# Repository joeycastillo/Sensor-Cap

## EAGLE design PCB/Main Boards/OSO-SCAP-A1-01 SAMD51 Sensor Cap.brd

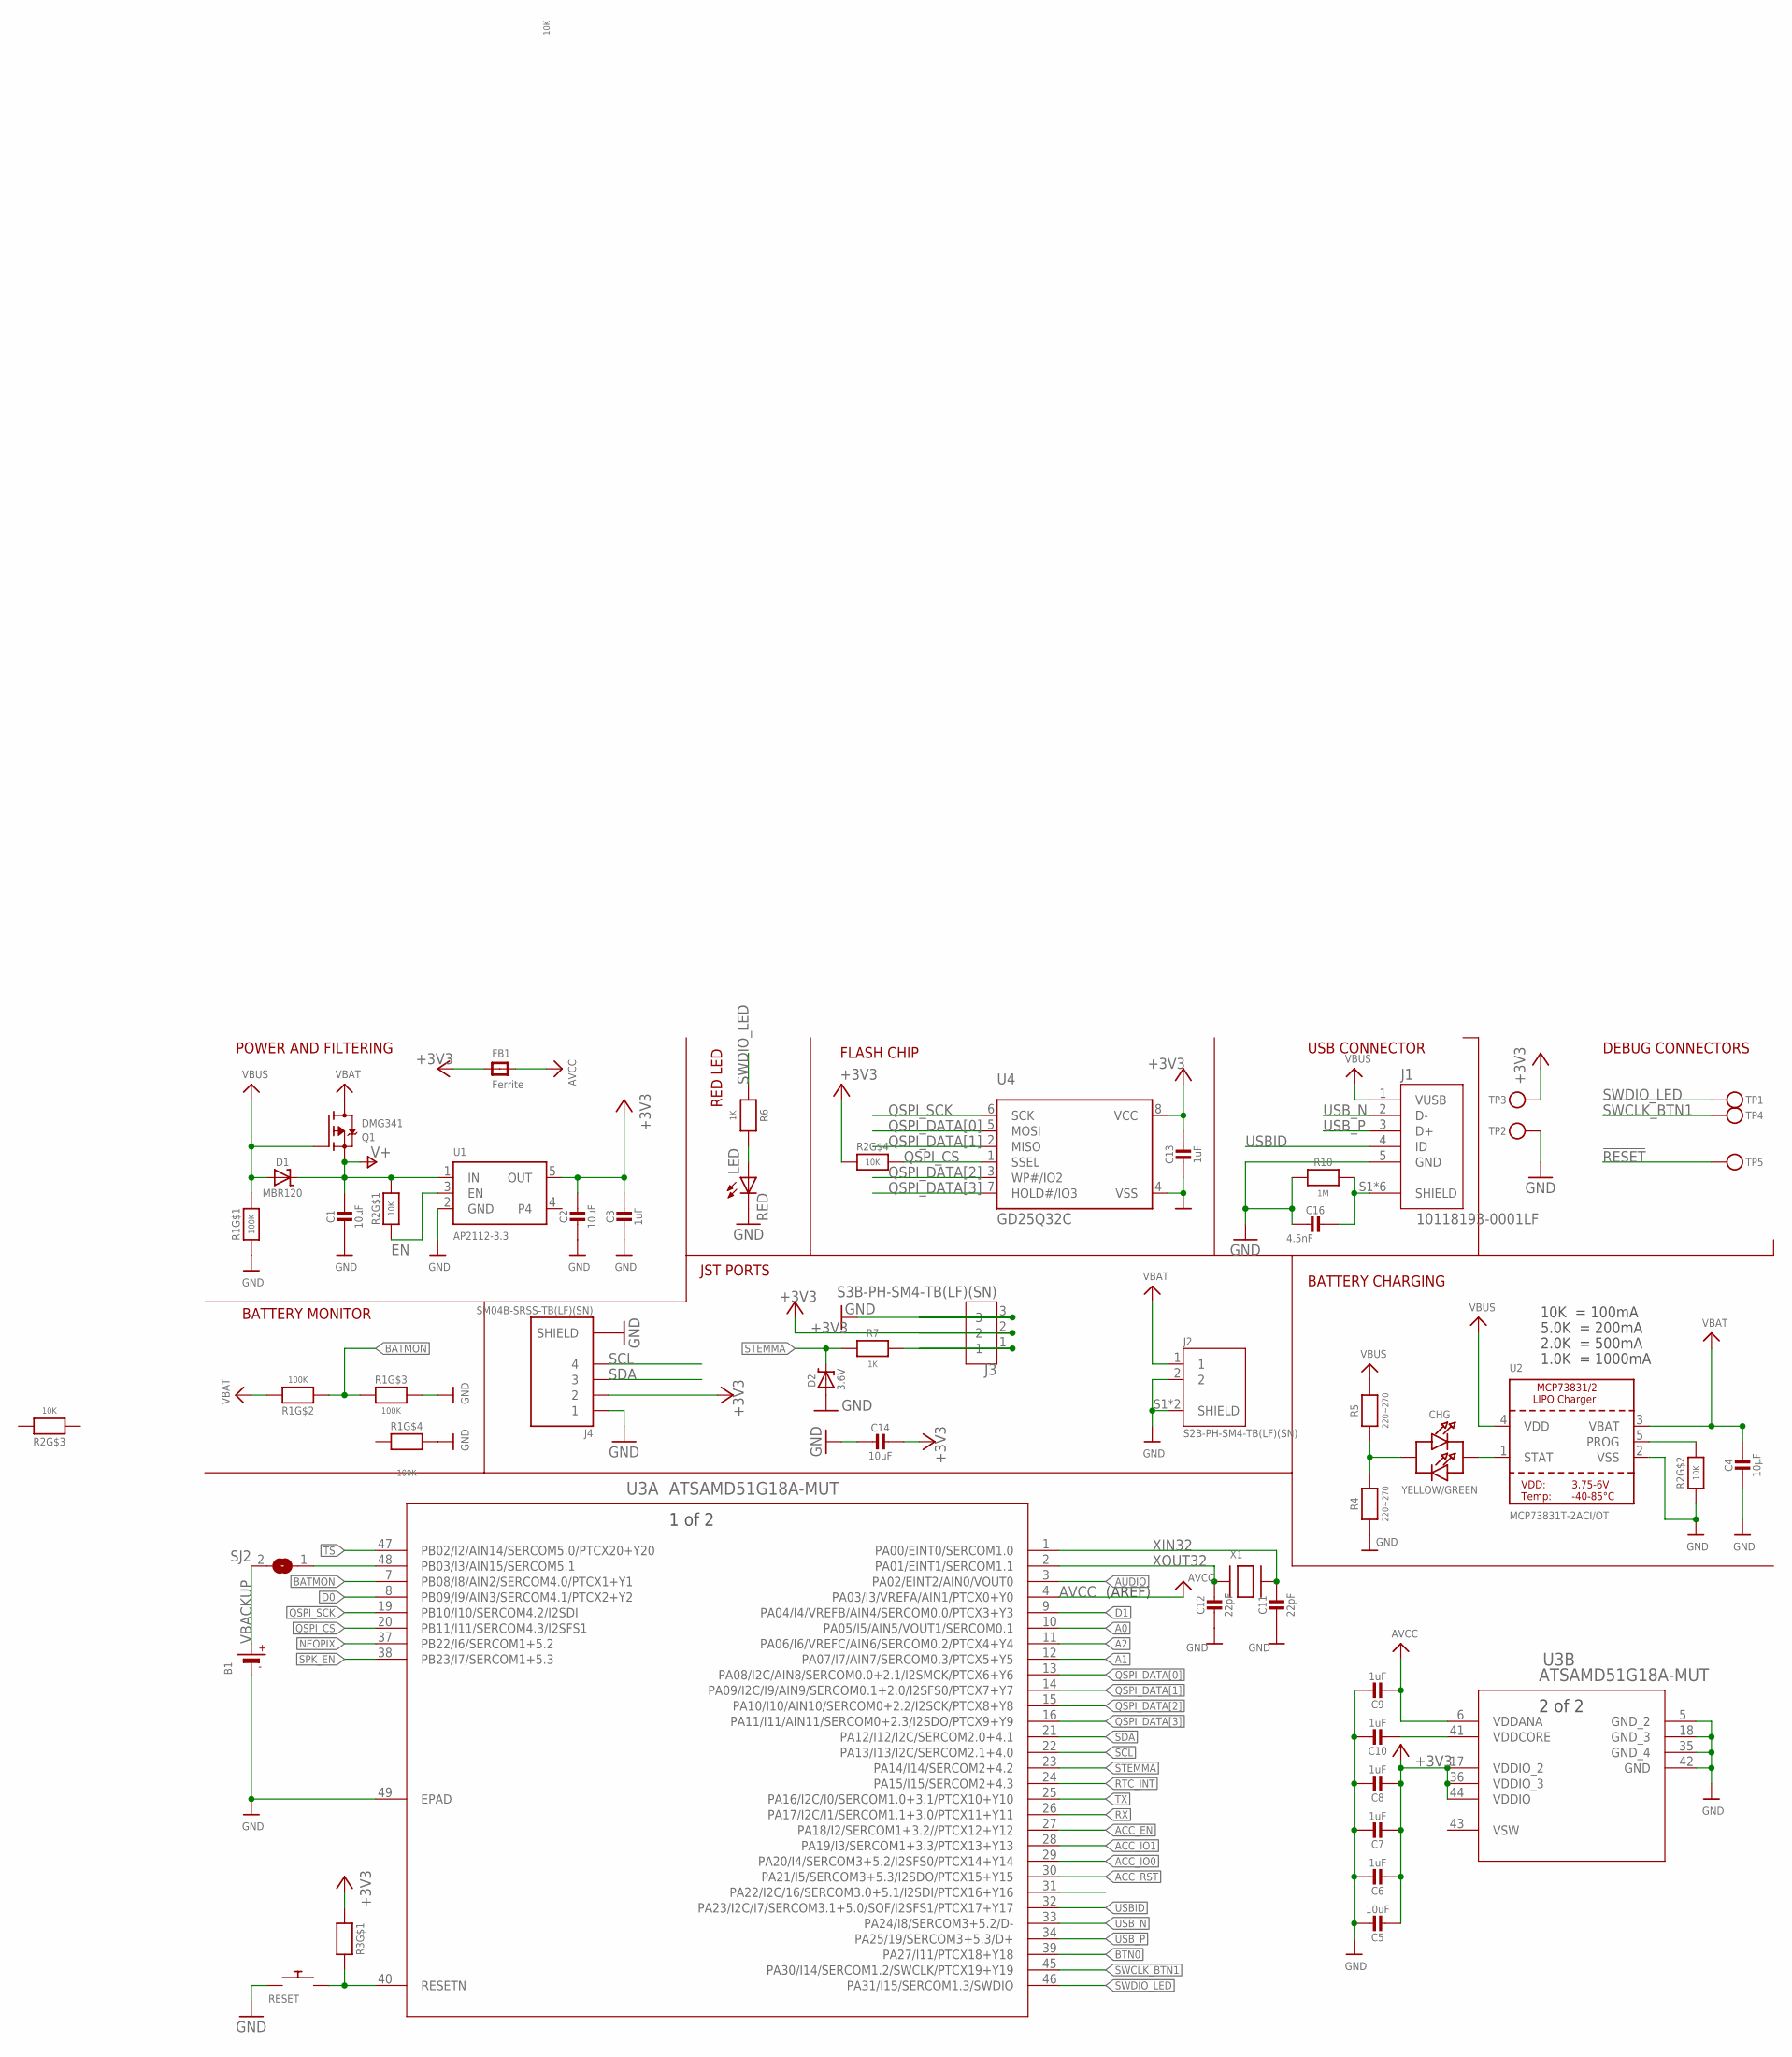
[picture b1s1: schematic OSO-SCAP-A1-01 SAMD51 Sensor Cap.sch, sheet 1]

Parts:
B1: CR1220; CR1220-2
C1, C2, C4: 10µF; 0805-NO
C3, C6, C7, C8, C13: 1uF; 0805-NO
C5: 10uF; 0805_10MGAP
C9, C10: 1uF; 0805_10MGAP
C11, C12: 22pF; 0805-NO
C14: 10uF; 0805-NO
C16: 4.5nF; 0805-NO
CHG: YELLOW/GREEN; CHIPLED_1206
D1: MBR120; SOD-123
D2: 3.6V; SOD-123
FB1: Ferrite; _0805MP
J1: 10118193-0001LF; FCI_10118193-0001LF
J2: S2B-PH-SM4-TB(LF)(SN); JST_S2B-PH-SM4-TB(LF)(SN)
J3: S3B-PH-SM4-TB(LF)(SN); JST_S3B-PH-SM4-TB(LF)(SN)
J4: SM04B-SRSS-TB(LF)(SN); JST_SM04B-SRSS-TB(LF)(SN)
LED: RED; CHIPLED_1206
Q1: DMG341; SOT23-R
R1: 100K; EXBV8V
R2, R3: 10K; EXBV8V
R4, R5: 220~270; 0805-NO
R6, R7: 1K; 0805-NO
R10: 1M; 0805-NO
RESET: SWITCH_PUSHBUTTONC&K_KSS; BTN_CK_KSS
SJ2: SOLDERJUMPERREFLOW_NOPASTE; SOLDERJUMPER_REFLOW_NOPASTE
TP1, TP2, TP3, TP4, TP5: TESTPOINTROUND1.5MMNO; TESTPOINT_ROUND_1.5MM_NO
U1: AP2112-3.3; SOT23-5
U2: MCP73831T-2ACI/OT; SOT23-5
U3: ATSAMD51G18A-MUT; QFN48_7X7MC
U4: GD25Q32C; MICROBUILDER_SOIC8_150MIL
X1: XTAL-3.2X1.5; XTAL3215

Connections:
!RESET: R3.8 (2), RESET.P$2, TP5.P$1, U3.40 (RESETN)
+3V3: C2.1, C3.1, C5.2, C6.2, C7.2, C8.2, C13.1, C14.1, FB1.1, J3.2, J4.2, R2.4 (1), R3.1, TP3.P$1, U1.5 (OUT), U3.17 (VDDIO_2), U3.36 (VDDIO_3), U3.44 (VDDIO), U4.8 (VCC); also elsewhere on the board
A0: U3.10 (PA05/I5/AIN5/VOUT1/SERCOM0.1); also elsewhere on the board
A1: U3.12 (PA07/I7/AIN7/SERCOM0.3/PTCX5+Y5); also elsewhere on the board
A2: U3.11 (PA06/I6/VREFC/AIN6/SERCOM0.2/PTCX4+Y4); also elsewhere on the board
ACC_EN: U3.27 (PA18/I2/SERCOM1+3.2//PTCX12+Y12); also elsewhere on the board
ACC_IO0: U3.29 (PA20/I4/SERCOM3+5.2/I2SFS0/PTCX14+Y14); also elsewhere on the board
ACC_IO1: U3.28 (PA19/I3/SERCOM1+3.3/PTCX13+Y13); also elsewhere on the board
ACC_RST: U3.30 (PA21/I5/SERCOM3+5.3/I2SDO/PTCX15+Y15); also elsewhere on the board
AUDIO: U3.3 (PA02/EINT2/AIN0/VOUT0); also elsewhere on the board
AVCC: C9.2, FB1.2, U3.4 (PA03/I3/VREFA/AIN1/PTCX0+Y0), U3.6 (VDDANA); also elsewhere on the board
BATMON: R1.2 (1), R1.3 (1), U3.7 (PB08/I8/AIN2/SERCOM4.0/PTCX1+Y1)
BTN0: U3.39 (PA27/I11/PTCX18+Y18); also elsewhere on the board
D0: U3.8 (PB09/I9/AIN3/SERCOM4.1/PTCX2+Y2); also elsewhere on the board
D1: U3.9 (PA04/I4/VREFB/AIN4/SERCOM0.0/PTCX3+Y3); also elsewhere on the board
EN: R2.1, U1.3 (EN); also elsewhere on the board
GND: B1.-, C1.2, C2.2, C3.2, C4.2, C5.1, C6.1, C7.1, C8.1, C9.1, C10.1, C11.2, C12.2, C13.2, C14.2, C16.2, D2.A, J1.5 (GND), J2.2, J2.S1 (SHIELD), J2.S2 (SHIELD), J3.3, J4.1, J4.S1 (SHIELD), J4.S2 (SHIELD), LED.C, R1.1, R1.5 (2), R1.6 (2), R2.2 (1), R4.1, R10.2, RESET.P$1, TP2.P$1, U1.2 (GND), U2.2 (VSS), U3.5 (GND_2), U3.18 (GND_3), U3.35 (GND_4), U3.42 (GND), U3.49 (EPAD), U4.4 (VSS); also elsewhere on the board
unnamed: CHG.A, R4.2, R5.1
unnamed: LED.A, R6.2
NEOPIX: U3.37 (PB22/I6/SERCOM1+5.2); also elsewhere on the board
PROG: R2.7 (2), U2.5 (PROG)
QSPI_CS: R2.5 (2), U3.20 (PB11/I11/SERCOM4.3/I2SFS1), U4.1 (SSEL)
QSPI_DATA[0]: U3.13 (PA08/I2C/AIN8/SERCOM0.0+2.1/I2SMCK/PTCX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), U4.5 (MOSI)
QSPI_DATA[1]: U3.14 (PA09/I2C/I9/AIN9/SERCOM0.1+2.0/I2SFS0/P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), U4.2 (MISO)
QSPI_DATA[2]: U3.15 (PA10/I10/AIN10/SERCOM0+2.2/I2SCK/PTCX8+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), U4.3 (WP#/IO2)
QSPI_DATA[3]: U3.16 (PA11/I11/AIN11/SERCOM0+2.3/I2SDO/PTCX9+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), U4.7 (HOLD#/IO3)
QSPI_SCK: U3.19 (PB10/I10/SERCOM4.2/I2SDI), U4.6 (SCK)
RTC_INT: U3.24 (PA15/I15/SERCOM2+4.3); also elsewhere on the board
RX: U3.26 (PA17/I2C/I1/SERCOM1.1+3.0/PTCX11+Y11); also elsewhere on the board
SCL: J4.4, U3.22 (PA13/I13/I2C/SERCOM2.1+4.0); also elsewhere on the board
SDA: J4.3, U3.21 (PA12/I12/I2C/SERCOM2.0+4.1); also elsewhere on the board
SHIELD: C16.1, J1.S1 (SHIELD), J1.S2 (SHIELD), J1.S3 (SHIELD), J1.S4 (SHIELD), J1.S5 (SHIELD), J1.S6 (SHIELD), R10.1
SPK_EN: U3.38 (PB23/I7/SERCOM1+5.3); also elsewhere on the board
STAT: CHG.C, U2.1 (STAT)
STEMMA: D2.C, R7.2, U3.23 (PA14/I14/SERCOM2+4.2)
SWCLK_BTN1: TP4.P$1, U3.45 (PA30/I14/SERCOM1.2/SWCLK/PTCX19+Y19); also elsewhere on the board
SWDIO_LED: R6.1, TP1.P$1, U3.46 (PA31/I15/SERCOM1.3/SWDIO)
TS: U3.47 (PB02/I2/AIN14/SERCOM5.0/PTCX20+Y20); also elsewhere on the board
TX: U3.25 (PA16/I2C/I0/SERCOM1.0+3.1/PTCX10+Y10); also elsewhere on the board
USBID: J1.4 (ID), U3.32 (PA23/I2C/I7/SERCOM3.1+5.0/SOF/I2SFS1/PT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)
USB_N: J1.2 (D-), U3.33 (PA24/I8/SERCOM3+5.2/D-)
USB_P: J1.3 (D+), U3.34 (PA25/19/SERCOM3+5.3/D+)
V+: C1.1, D1.C, Q1.2 (S), R2.8 (2), U1.1 (IN)
VBACKUP: B1.+, SJ2.2; also elsewhere on the board
VBAT: C4.1, J2.1, Q1.3 (D), R1.7 (2), U2.3 (VBAT)
VBUS: D1.A, J1.1 (VUSB), Q1.1 (G), R1.8 (2), R5.2, U2.4 (VDD)
VDDCORE: C10.2, U3.41 (VDDCORE)
VSW: U3.43 (VSW)
XIN32: C11.1, U3.1 (PA00/EINT0/SERCOM1.0), X1.P$2
XOUT32: C12.1, U3.2 (PA01/EINT1/SERCOM1.1), X1.P$1
_STEMMA: J3.1, R7.1
_VBACKUP: SJ2.1, U3.48 (PB03/I3/AIN15/SERCOM5.1)

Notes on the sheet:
POWER AND FILTERING
10K = 100mA
5.0K = 200mA
2.0K = 500mA
1.0K = 1000mA
BATTERY CHARGING
DEBUG CONNECTORS
USB CONNECTOR
BATTERY MONITOR
FLASH CHIP
RED LED
JST PORTS
(AREF)

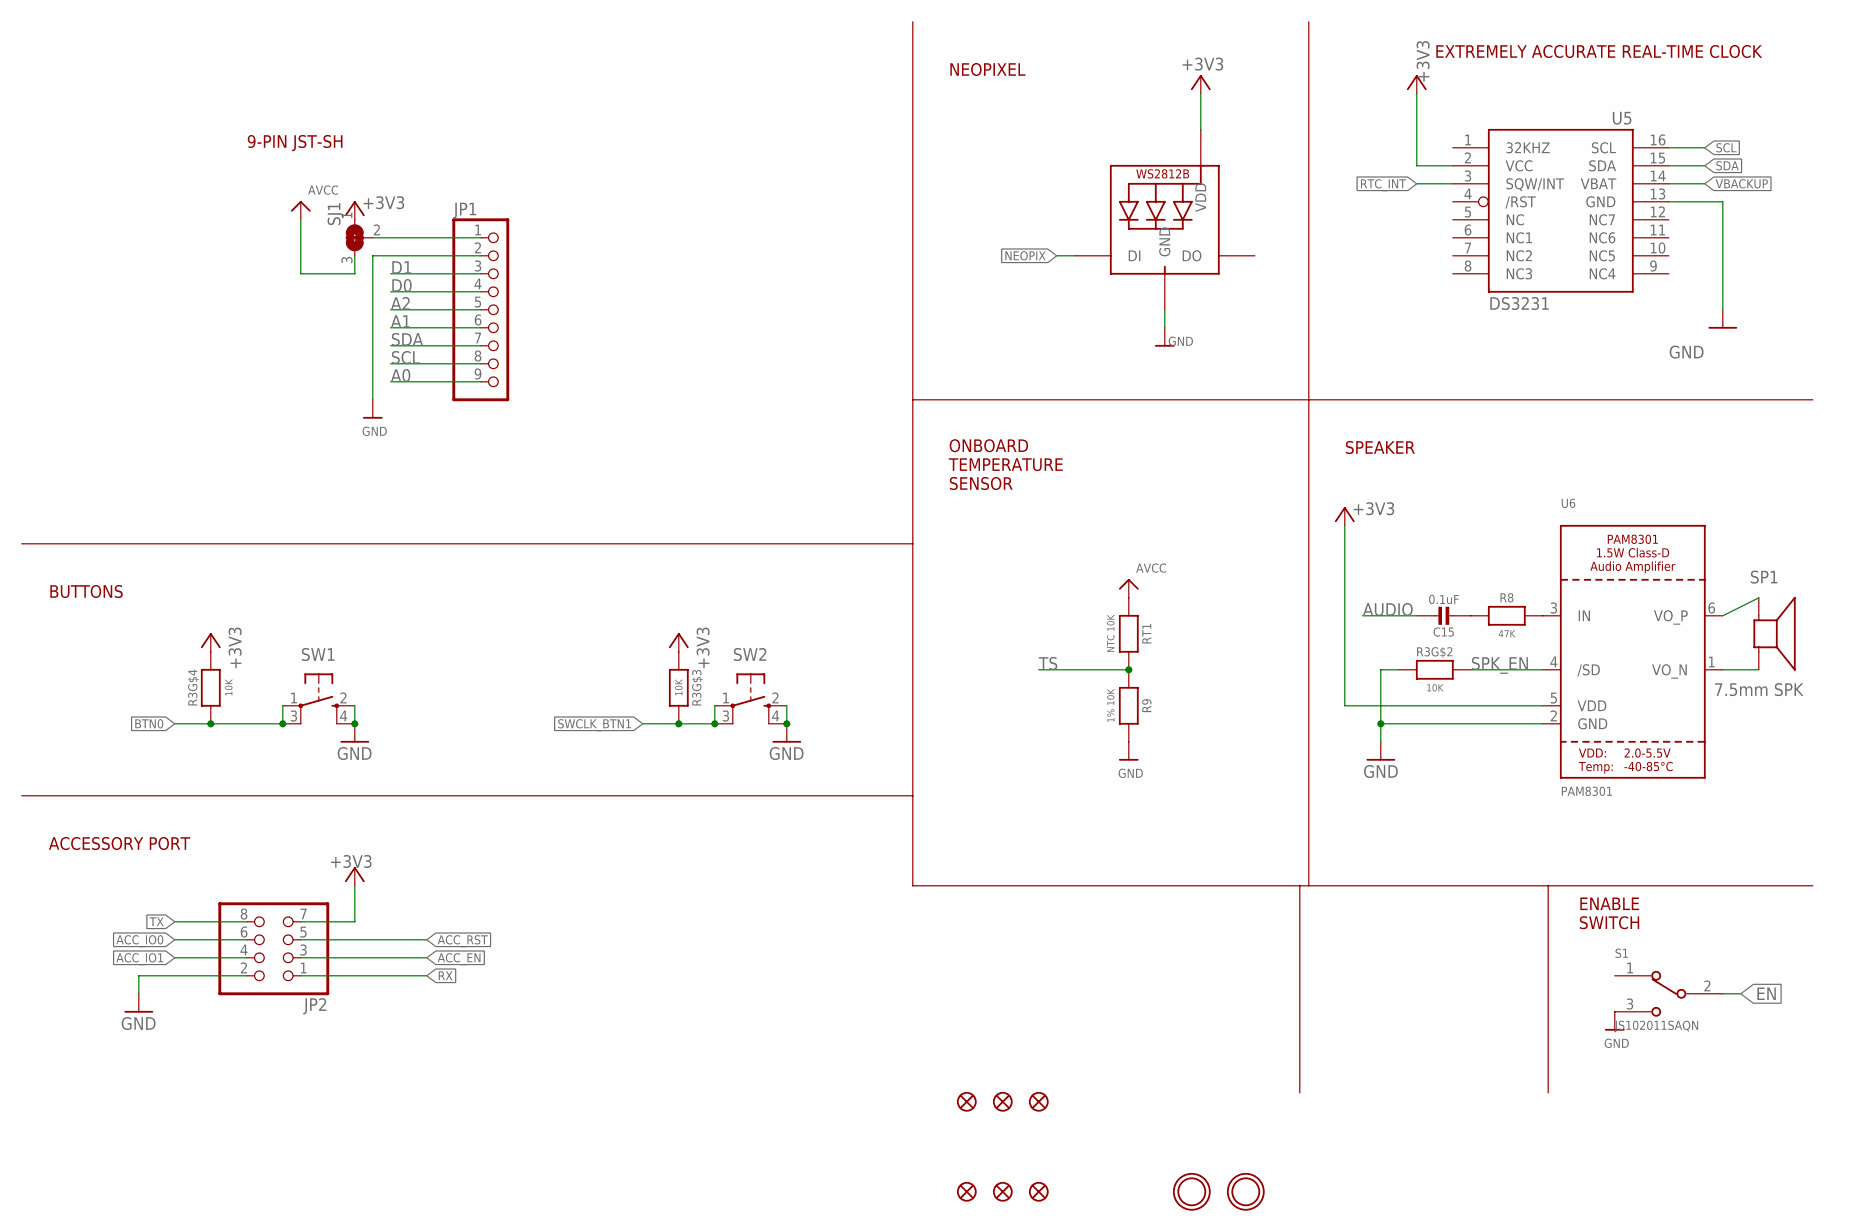
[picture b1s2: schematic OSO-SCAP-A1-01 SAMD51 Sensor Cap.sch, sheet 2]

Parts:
C15: 0.1uF; 0805-NO
FID1, FID2, FID3, FID4, FID5, FID6: FIDUCIAL_1MM
JP1: HEADER-1X9_JSTSH; JST_SH9
JP2: PINHD-2X4SMT; PINHD_2X4_SMT
NEOPIX: WS2812B_4020
R3: 10K; EXBV8V
R8: 47K; 0805-NO
R9: 1% 10K; 0805-NO
RT1: NTC 10K; 0805-NO
S1: JS102011SAQN; SW_JS102011SAQN
SJ1: SOLDERJUMPER_2WAY; SOLDERJUMPER_2WAY_OPEN_NOPASTE
SP1: 7.5mm SPK; BUZZER_SMT_5MM
SW1, SW2: SPST_TACT-KMR2; KMR2
U5: DS3231/SO; SO16W
U6: PAM8301; SOT23-6
U$1, U$4: MOUNTINGHOLE2.5; MOUNTINGHOLE_2.5_PLATED

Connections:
+3V3: JP2.7, NEOPIX.2 (VDD), R3.3 (1), R3.5 (2), SJ1.1, U5.2 (VCC), U6.5 (VDD); also elsewhere on the board
A0: JP1.9; also elsewhere on the board
A1: JP1.6; also elsewhere on the board
A2: JP1.5; also elsewhere on the board
ACC_EN: JP2.3; also elsewhere on the board
ACC_IO0: JP2.6; also elsewhere on the board
ACC_IO1: JP2.4; also elsewhere on the board
ACC_RST: JP2.5; also elsewhere on the board
AUDIO: C15.1; also elsewhere on the board
AVCC: RT1.1, SJ1.3; also elsewhere on the board
BTN0: R3.4 (1), SW1.1, SW1.3 (P1); also elsewhere on the board
D0: JP1.4; also elsewhere on the board
D1: JP1.3; also elsewhere on the board
EN: S1.2; also elsewhere on the board
GND: JP1.2, JP2.2, NEOPIX.4 (GND), R3.2 (1), R9.2, S1.3, SW1.2 (S), SW1.4 (S1), SW2.2 (S), SW2.4 (S1), U5.13 (GND), U6.2 (GND); also elsewhere on the board
unnamed: C15.2, R8.1
unnamed: R8.2, U6.3 (IN)
NEOPIX: NEOPIX.1 (DI); also elsewhere on the board
POWER_OUT: JP1.1, SJ1.2
RTC_INT: U5.3 (SQW/INT); also elsewhere on the board
RX: JP2.1; also elsewhere on the board
SCL: JP1.8, U5.16 (SCL); also elsewhere on the board
SDA: JP1.7, U5.15 (SDA); also elsewhere on the board
SPK_EN: R3.7 (2), U6.4 (/SD); also elsewhere on the board
SPK_N: SP1.+, U6.1 (VO_N)
SPK_P: SP1.-, U6.6 (VO_P)
SWCLK_BTN1: R3.6 (2), SW2.1, SW2.3 (P1); also elsewhere on the board
TS: R9.1, RT1.2; also elsewhere on the board
TX: JP2.8; also elsewhere on the board
VBACKUP: U5.14 (VBAT); also elsewhere on the board

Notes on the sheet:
ENABLE SWITCH
9-PIN JST-SH
ONBOARD TEMPERATURE SENSOR
BUTTONS
ACCESSORY PORT
NEOPIXEL
EXTREMELY ACCURATE REAL-TIME CLOCK
SPEAKER

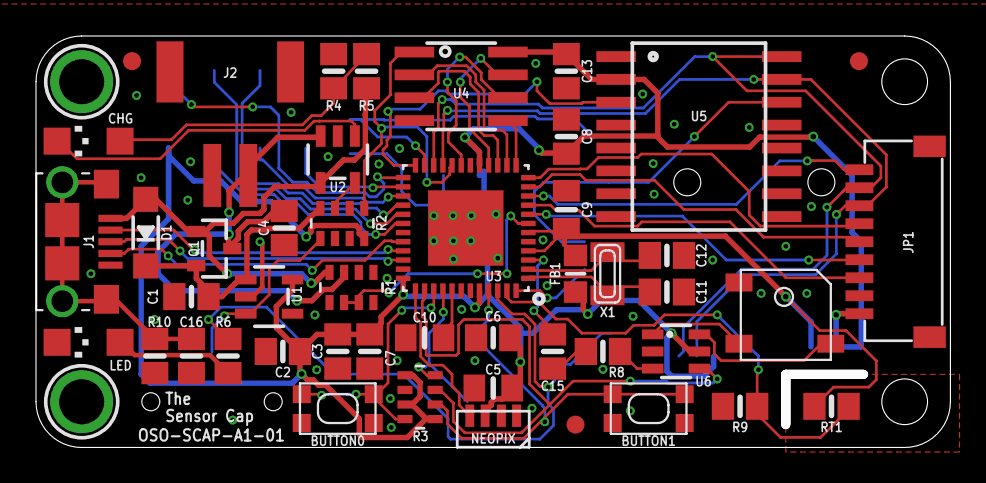
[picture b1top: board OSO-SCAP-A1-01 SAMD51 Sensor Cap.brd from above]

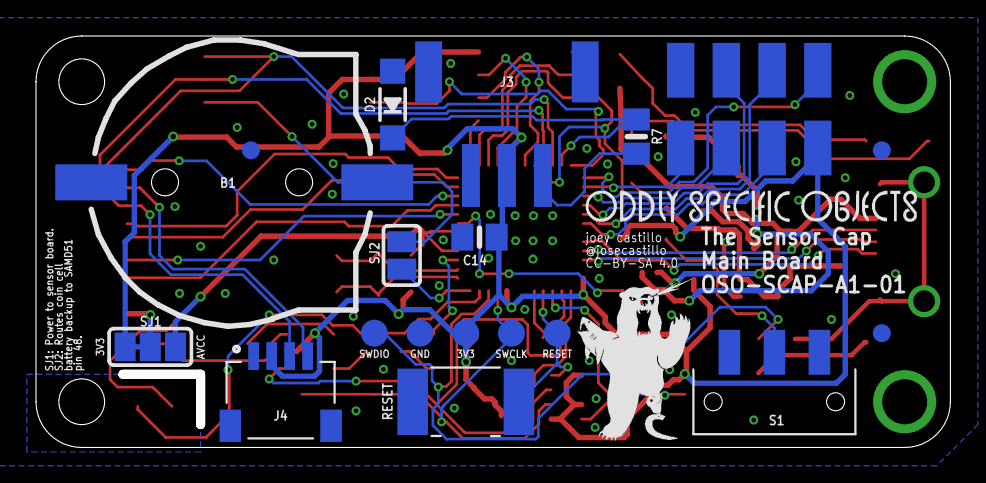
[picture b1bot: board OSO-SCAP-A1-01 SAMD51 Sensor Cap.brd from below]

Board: 2 copper layers, 50.8 x 22.9 mm, 70 parts (21 on the bottom side), 56 nets.

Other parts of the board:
U$31: OSO_WORDMARK_ONELINE_725MIL_1000DPI
U$32: OSO_BEAR_250X360MIL_1000DPI

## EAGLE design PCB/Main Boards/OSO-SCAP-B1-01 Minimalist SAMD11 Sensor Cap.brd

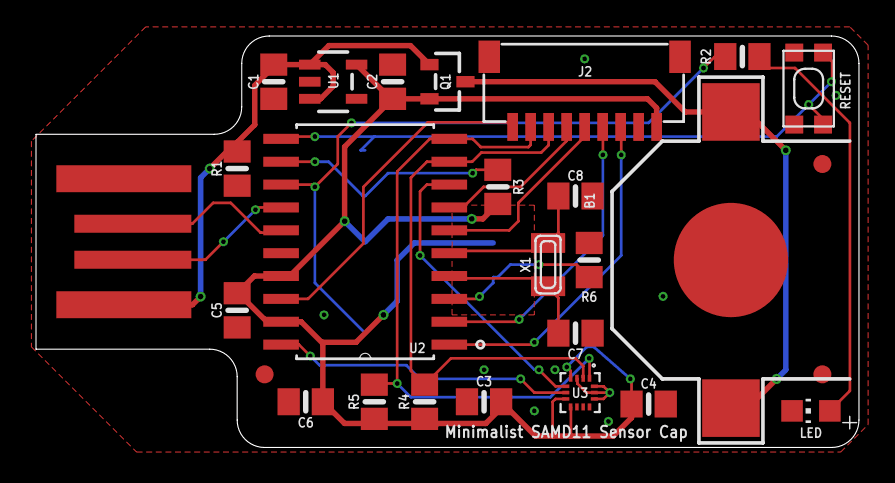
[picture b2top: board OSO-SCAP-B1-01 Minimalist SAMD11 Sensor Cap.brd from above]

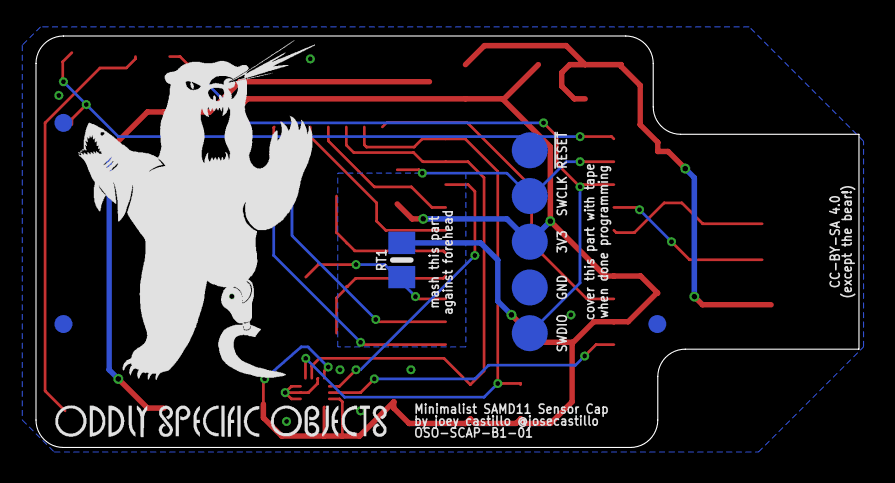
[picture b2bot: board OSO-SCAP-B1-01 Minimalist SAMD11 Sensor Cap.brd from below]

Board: 2 copper layers, 45.7 x 22.9 mm, 38 parts (11 on the bottom side), 22 nets.

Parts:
B1: CR1220
C1, C2, C4: 10µF; 0805-NO
C3: 0.1uF; 0805-NO
C5: 10uF; 0805-NO
C6: 1uF; 0805-NO
C7, C8: 22pF; 0805-NO
FID1, FID2, FID3, FID4, FID5, FID6: FIDUCIAL_1MM
J1: USBPCB; USB-A-PCB
J2: JST_SH9
LED: ORANGE; CHIP-LED0805
Q1: DMG341; SOT23-R
R1: 100K; 0805-NO
R2: 2.2K; 0805-NO
R3, R4, R5: 50K; 0805-NO
R6: 100K/1%; 0805-NO
RT1: NTC 100K; 0805-NO
SW1: SPST_TACT-KMR2; KMR2
TP1, TP2, TP3, TP4, TP5: TESTPOINT_ROUND_2MM_NO
U1: AP2112-3.3; SOT23-5
U2: ATSAMD11D14A-SSNT; SOIC127P1030X265-20N
U3: LIS2DHTR; PQFN35P200X200X100-14N
U$16: OSO_BEAR_525X750MIL_1000DPI
U$21: OSO_WORDMARK_ONELINE_725MIL_1000DPI
X1: XTAL3215

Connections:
!RESET: SW1.2, SW1.4, TP5.P$1, U2.11
+3V3: C2.1, C3.2, C4.1, C5.1, C6.1, J2.1, Q1.2, R3.1, R4.1, R5.1, RT1.1, TP3.P$1, U1.5, U2.17, U2.19, U3.4, U3.7, U3.8
GND: B1.-, C1.2, C2.2, C3.1, C4.2, C5.2, C6.2, C7.2, C8.2, J1.GND, J2.2, LED.C, R1.2, R6.2, SW1.1, SW1.3, TP2.P$1, U1.2, U2.16, U3.3, U3.9, U3.10, U3.11, U3.12, U3.13, U3.14
unnamed: LED.A, R2.2
PA02: J2.9, U2.18
PA04: U2.20, U3.6
PA05: J2.3, U2.1
PA06: J2.4, U2.2
PA07: R6.1, RT1.2, U2.3
PA14: J2.5, U2.6
PA15: J2.6, U2.7
PA16: U2.8, U3.5
PA22/SDA: J2.7, R4.2, U2.9, U3.2
PA23/SCL: J2.8, R5.2, U2.10, U3.1
PA30/SWCLK: R3.2, TP4.P$1, U2.12
PA31/SWDIO/LED: R2.1, TP1.P$1, U2.13
USB_N: J1.USB_M, U2.14
USB_P: J1.USB_P, U2.15
VBAT: B1.+$1, B1.+$2, Q1.3
VBUS: C1.1, J1.5V, Q1.1, R1.1, U1.1, U1.3
XIN32: C7.1, U2.4, X1.P$1
XOUT32: C8.1, U2.5, X1.P$2

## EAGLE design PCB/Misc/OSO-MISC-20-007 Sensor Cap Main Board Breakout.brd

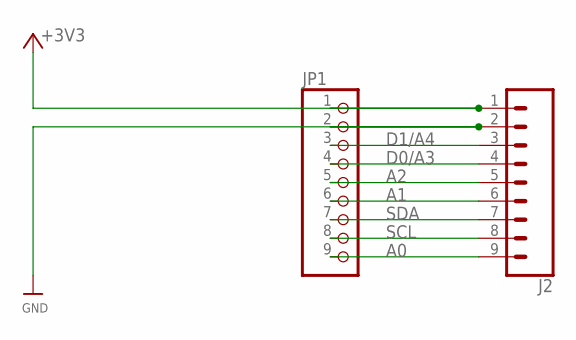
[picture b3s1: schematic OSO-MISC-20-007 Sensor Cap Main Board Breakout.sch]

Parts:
J2: CONN_09NO_SILK; 1X09_NO_SILK
JP1: HEADER-1X9_JSTSH; JST_SH9

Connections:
+3V3: J2.1, JP1.1
A0: J2.9, JP1.9
A1: J2.6, JP1.6
A2: J2.5, JP1.5
D0/A3: J2.4, JP1.4
D1/A4: J2.3, JP1.3
GND: J2.2, JP1.2
SCL: J2.8, JP1.8
SDA: J2.7, JP1.7

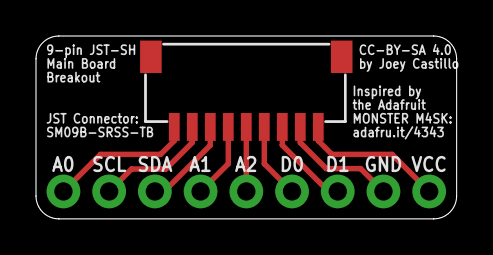
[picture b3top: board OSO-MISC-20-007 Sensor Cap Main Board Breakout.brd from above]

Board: 2 copper layers, 23.4 x 10.2 mm, 3 parts (1 on the bottom side), 9 nets.

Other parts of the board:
U$1: OSO_WORDMARK_ONELINE_725MIL_1000DPI

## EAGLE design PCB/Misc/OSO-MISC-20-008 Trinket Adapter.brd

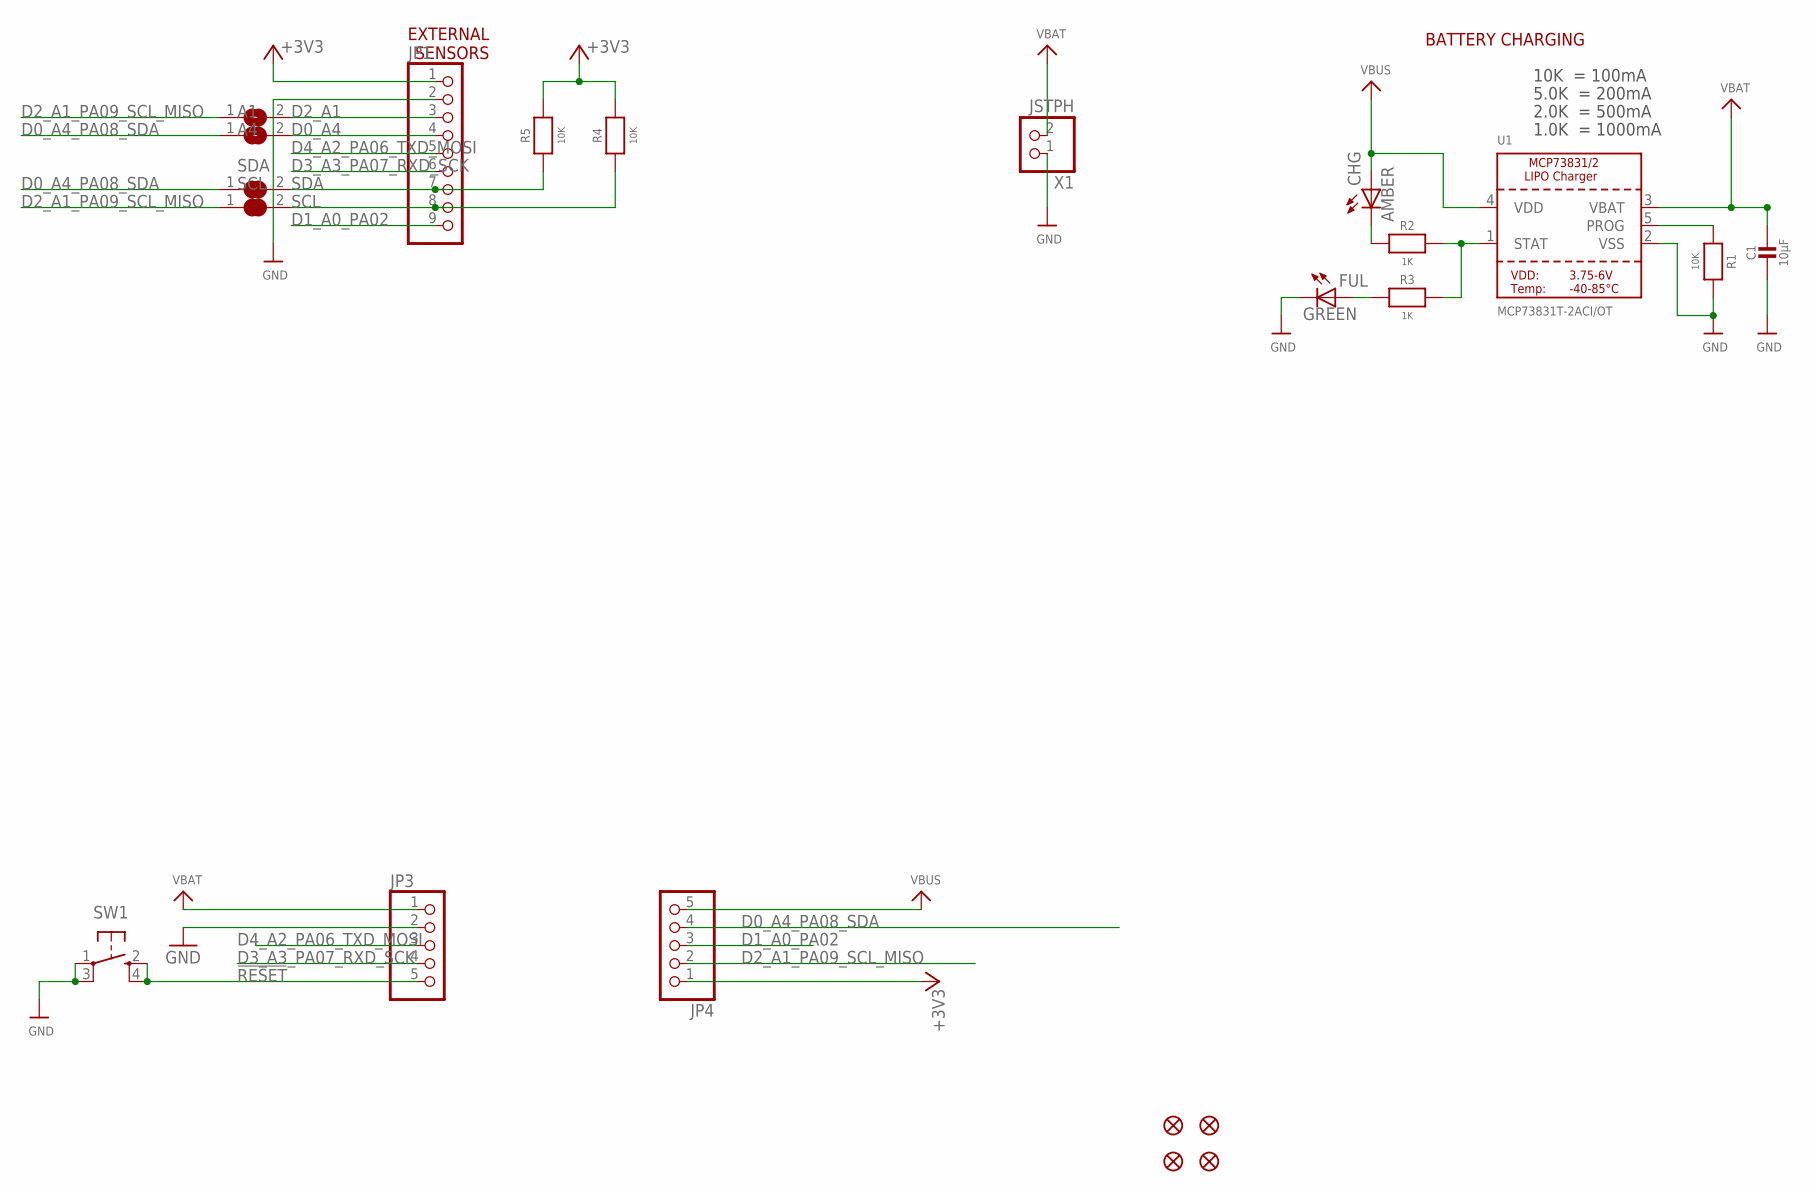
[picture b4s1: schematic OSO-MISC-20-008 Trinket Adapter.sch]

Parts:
A1, A4: SOLDERJUMPERREFLOW_NOPASTE; SOLDERJUMPER_REFLOW_NOPASTE
C1: 10µF; 0805-NO
CHG: AMBER; CHIPLED_0805
FID1, FID2, FID3, FID4: FIDUCIAL_1MM
FUL: GREEN; CHIPLED_0805
JP1: HEADER-1X9_JSTSH; JST_SH9
JP3, JP4: HEADER-1X576MIL; 1X05_ROUND_76
R1, R4, R5: 10K; 0805-NO
R2, R3: 1K; 0805-NO
SCL: MICROBUILDER_SOLDERJUMPER_CLOSED; MICROBUILDER_SOLDERJUMPER_CLOSEDWIRE
SDA: MICROBUILDER_SOLDERJUMPER_CLOSED; MICROBUILDER_SOLDERJUMPER_CLOSEDWIRE
SW1: SPST_TACT-KMR2; KMR2
U1: MCP73831T-2ACI/OT; SOT23-5
X1: JSTPH; JSTPH2

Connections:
!RESET: JP3.5, SW1.2 (S), SW1.4 (S1)
+3V3: JP1.1, JP4.1, R4.2, R5.2
D0_A4: A4.2, JP1.4
D0_A4_PA08_SDA: A4.1, JP4.4, SDA.1
D1_A0_PA02: JP1.9, JP4.3
D2_A1: A1.2, JP1.3
D2_A1_PA09_SCL_MISO: A1.1, JP4.2, SCL.1
D3_A3_PA07_RXD_SCK: JP1.6, JP3.4
D4_A2_PA06_TXD_MOSI: JP1.5, JP3.3
GND: C1.2, FUL.C, JP1.2, JP3.2, R1.2, SW1.1, SW1.3 (P1), U1.2 (VSS), X1.1
unnamed: CHG.C, R2.1
unnamed: FUL.A, R3.1
PROG: R1.1, U1.5 (PROG)
SCL: JP1.8, R4.1, SCL.2
SDA: JP1.7, R5.1, SDA.2
STAT: R2.2, R3.2, U1.1 (STAT)
VBAT: C1.1, JP3.1, U1.3 (VBAT), X1.2
VBUS: CHG.A, JP4.5, U1.4 (VDD)

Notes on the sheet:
10K = 100mA
5.0K = 200mA
2.0K = 500mA
1.0K = 1000mA
BATTERY CHARGING
EXTERNAL SENSORS

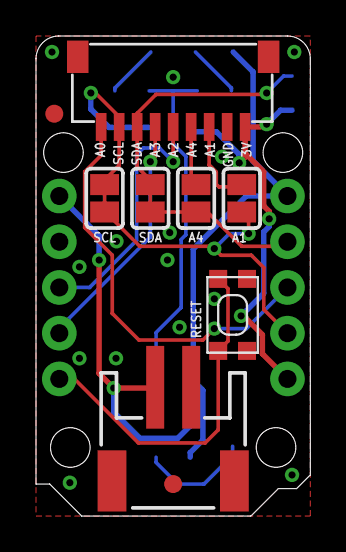
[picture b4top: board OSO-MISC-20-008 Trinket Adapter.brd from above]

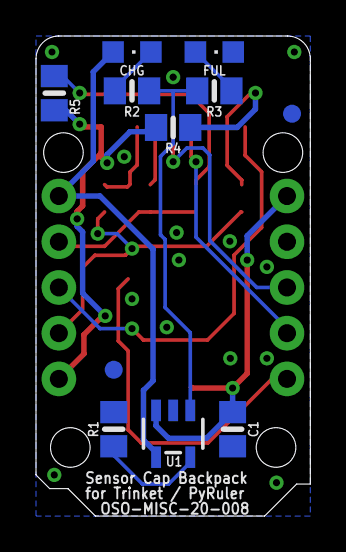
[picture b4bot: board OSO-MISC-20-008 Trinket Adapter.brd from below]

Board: 2 copper layers, 15.2 x 26.7 mm, 22 parts (11 on the bottom side), 18 nets.

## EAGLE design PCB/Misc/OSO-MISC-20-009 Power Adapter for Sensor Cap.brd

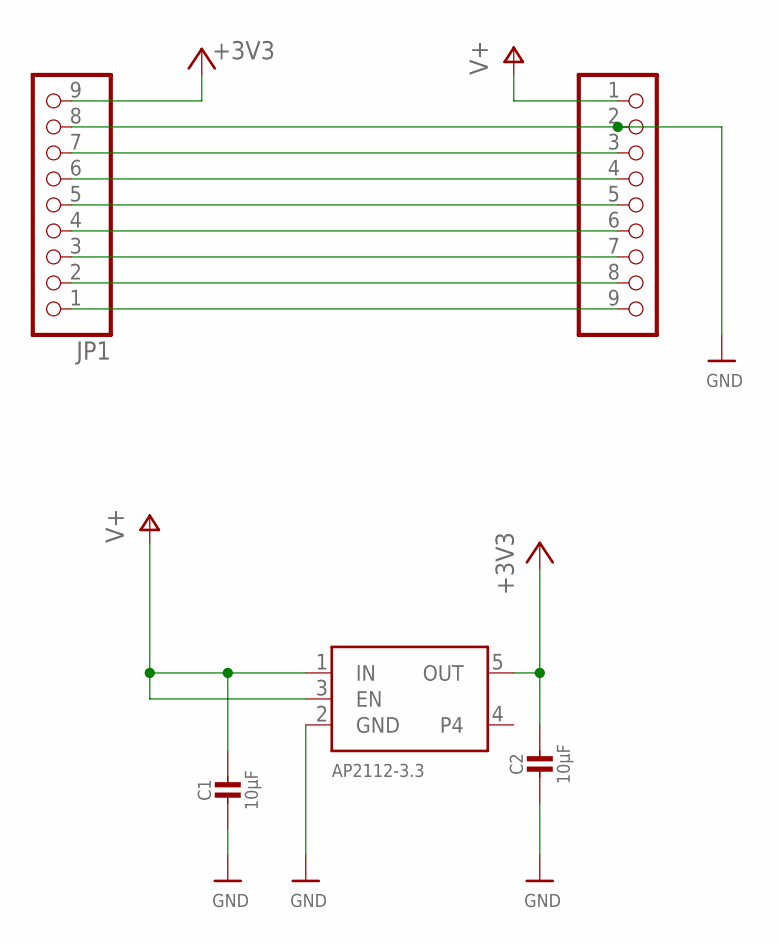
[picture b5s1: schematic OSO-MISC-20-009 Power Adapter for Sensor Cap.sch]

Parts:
C1, C2: 10µF; 0805-NO
JP1, JP2: HEADER-1X9_JSTSH; JST_SH9
U1: AP2112-3.3; SOT23-5

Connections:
+3V3: C2.1, JP1.9, U1.5 (OUT)
GND: C1.2, C2.2, JP1.8, JP2.2, U1.2 (GND)
unnamed: JP1.1, JP2.9
unnamed: JP1.2, JP2.8
unnamed: JP1.3, JP2.7
unnamed: JP1.4, JP2.6
unnamed: JP1.5, JP2.5
unnamed: JP1.6, JP2.4
unnamed: JP1.7, JP2.3
V+: C1.1, JP2.1, U1.1 (IN), U1.3 (EN)

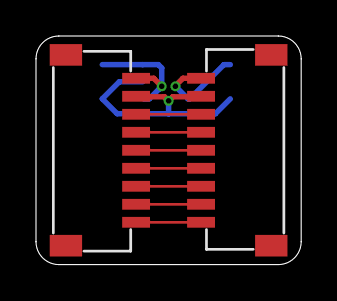
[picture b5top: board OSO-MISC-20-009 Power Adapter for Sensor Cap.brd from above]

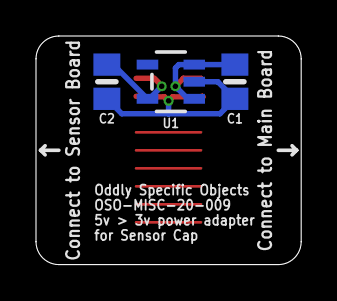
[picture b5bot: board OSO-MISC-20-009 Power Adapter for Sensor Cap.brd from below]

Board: 2 copper layers, 14.7 x 12.7 mm, 5 parts (3 on the bottom side), 10 nets.

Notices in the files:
PCB/Main Boards/OSO-SCAP-A1-01 SAMD51 Sensor Cap.brd:
CC-BY-SA 4.0
parts and their libraries:
COPYRIGHT: Copyright (C) 2018 Accelerated Designs. All rights reserved
microbuilder: This work is placed in the public domain, and may be freely used for commercial and non-commercial work with the following conditions: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
